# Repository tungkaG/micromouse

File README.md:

Code for Demo-mouse:

Current status:
Main control loop in timer interrupt (streamSensorData function):
1. update curr_cell or curr_heading, depending on the command that just took place (STOP, FORWARD, TURN_90_LEFT, TURN_90_RIGHT, TURN_180)
2. get next command (STOP, FORWARD, TURN_90_LEFT, TURN_90_RIGHT, TURN_180) using nextCmd(left_sensor_info, right_sensor_info, front_sensor_info)

Every time the mouse stops, the grid (details see below) is sent via UART and can be received using print_maze_and_send_forward_speed.py and 
the FORWARD_SPEED can be changed anytime by sending e.g. "<6>" via UART to the demomouse (i.e. sets FORWARD_SPEED to 6 rad/s)

The following only concerns highLevelPlanning.c :

In nextCmd(...): If the next cell is reached (curr_cell==next_cell), based on the state (IDLE, EXPLORING_PATH_TO_GOAL, EXPLORING_TEMP_BEST_PATH, RETURN_TO_START, DRIVE_TO_GOAL) the new next_cell is calculated:

EXPLORING_PATH_TO_GOAL: update grid matrix with sensor infos and find best next cell on the way to the goals (middle region) using Flood Fill Algorithm.

EXPLORING_TEMP_BEST_PATH: update grid matrix with sensor infos and find next cell with UNKNOWN walls that is part of the temporarily best path from start to goals.

RETURN_TO_START: update grid matrix with sensor infos and find best next cell on the way to cell {START_X, START_Y}

DRIVE_TO_GOAL: find best next cell on the path to goal using Flood Fill Algorithm

Then via translate_next_cell_to_cmd() check if the mouse should turn or if curr_heading == want_heading -> drive FORWARD

In general, grid is a matrix stored as grid[GRID_SIZE][GRID_SIZE][4], so for each cell, we store if UP, LEFT, DOWN and RIGHT (index 0 - 3) is WALL or is FREE. 

An example grid looks like this (note that y are the rows and x are the cols, so grid[curr_cell.y][curr_cell.x][UP] corresponds to the upper wall of the current cell:

' ' ' '
	UP

LEFT (x,y) RIGHT

' ' ' '
	DOWN

(0,0) (1,0)

(0,1)  ...

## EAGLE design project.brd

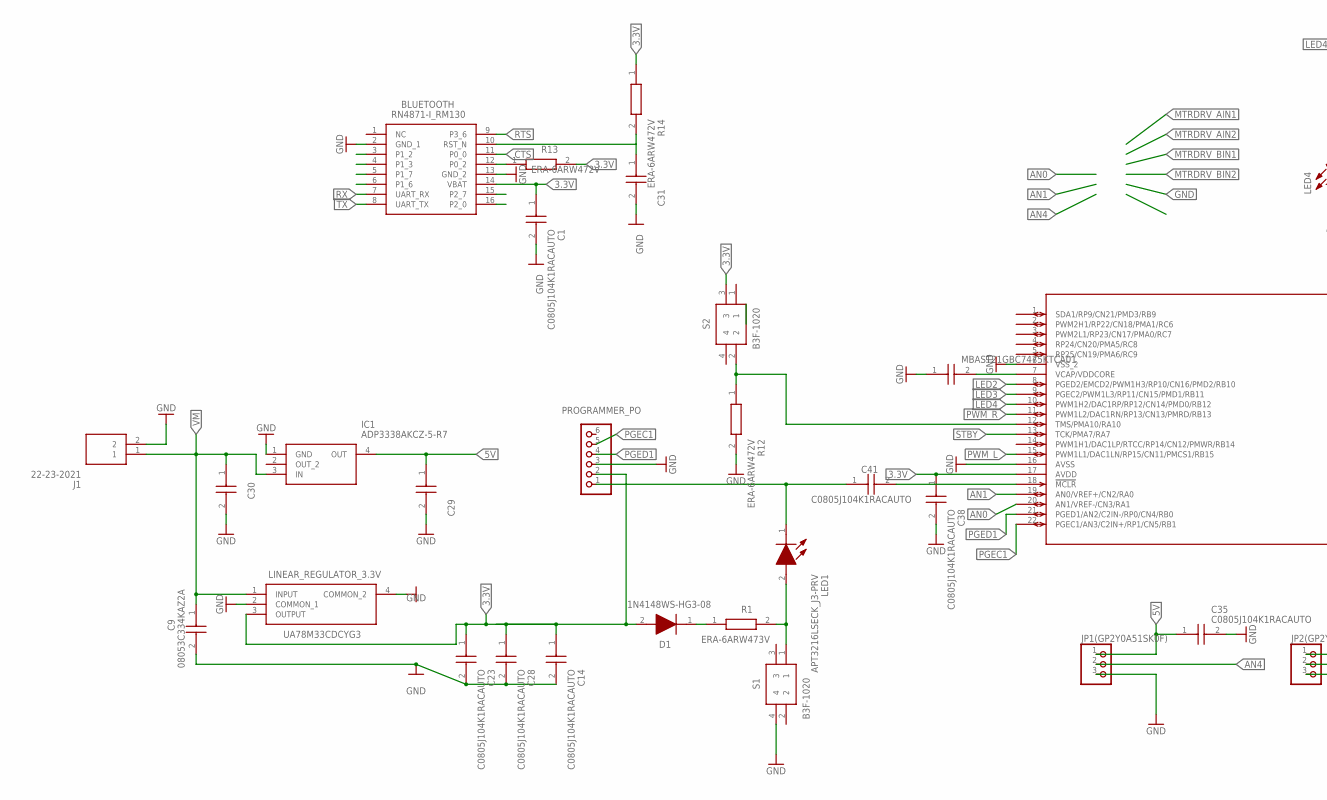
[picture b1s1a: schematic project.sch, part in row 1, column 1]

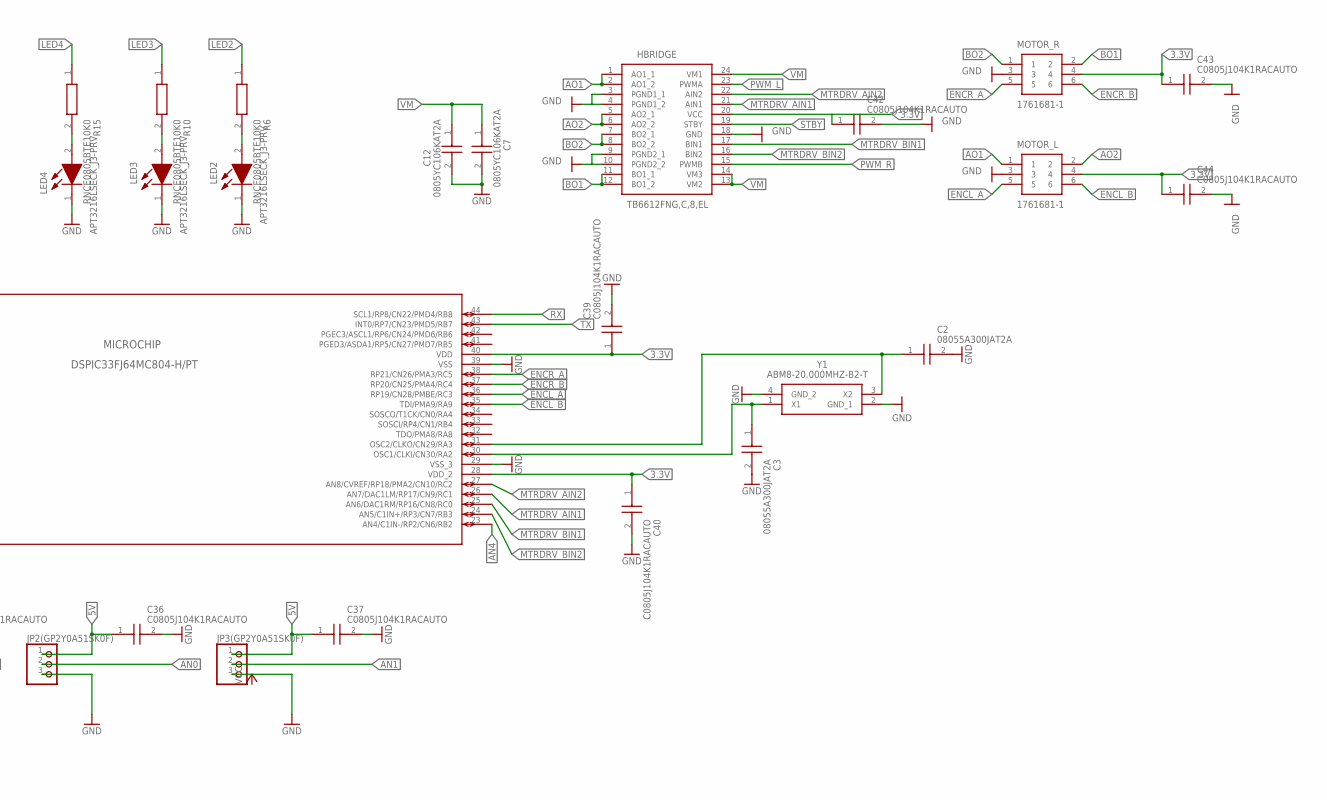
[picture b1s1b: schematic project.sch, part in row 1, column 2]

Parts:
BLUETOOTH: RN4871-I_RM130; RN4871
C1, C14, C23, C28, C29, C31, C35, C36, C37, C38, C39, C40, C41, C42, C43, C44: C0805J104K1RACAUTO; CAPC2012X140N
C2, C3: 08055A300JAT2A; CAPC2012X94N
C4: MBAST21GBC7475KTCA01; CAPC2114X145N
C7, C12: 0805YC106KAT2A; CAPC2012X94N
C9: 08053C334KAZ2A; CAPC2012X152N
C30: 1µF; CAPC2012X140N
D1: 1N4148WS-HG3-08; SOD2713X115N
HBRIDGE: TB6612FNG,C,8,EL; SOP65P760X160-24N
IC1: ADP3338AKCZ-5-R7; SOT230P700X180-4N
J1: 22-23-2021; SHDR2W87P0X254_1X2_493X635X110
JP1(GP2Y0A51SK0F), JP2(GP2Y0A51SK0F), JP3(GP2Y0A51SK0F): PINHD-1X3; 1X03
LED1, LED2, LED3, LED4: APT3216LSECK_J3-PRV; LEDC3216X95N
LINEAR_REGULATOR_3.3V: UA78M33CDCYG3; SOT230P700X180-4N
MICROCHIP: DSPIC33FJ64MC804-H/PT; TQFP44_10X10MC_MCH
MOTOR_L: 1761681-1; SHDR6W67P254_2X3_1524X916X922P
MOTOR_R: 1761681-1; SHDR6W67P254_2X3_1524X916X922P
PROGRAMMER_PO: PINHD-1X6; 1X06
R1: ERA-6ARW473V; ERA6AEB101V
R6, R10, R15: RNCE0805BTE10K0; RESC2012X65N
R12, R13, R14: ERA-6ARW472V; ERA6AEB101V
S1, S2: B3F-1020; B3F1000
Y1: ABM8-20.000MHZ-B2-T; ABM810000MHZ12D2W

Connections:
3.3V: BLUETOOTH.14 (VBAT), C1.1, C14.1, C23.1, C28.1, C38.1, C39.1, C40.1, C42.1, C43.1, C44.1, D1.2 (A), HBRIDGE.20 (VCC), LINEAR_REGULATOR_3.3V.3 (OUTPUT), MICROCHIP.17 (AVDD), MICROCHIP.28 (VDD_2), MICROCHIP.40 (VDD), MOTOR_L.4, MOTOR_R.4, PROGRAMMER_PO.2, R13.2, R14.1, S2.3
5V: C29.1, C35.1, C36.1, C37.1, IC1.4 (OUT), JP1(GP2Y0A51SK0F).1, JP2(GP2Y0A51SK0F).1, JP3(GP2Y0A51SK0F).1
AN0: JP2(GP2Y0A51SK0F).2, MICROCHIP.20 (AN1/VREF-/CN3/RA1)
AN1: JP3(GP2Y0A51SK0F).2, MICROCHIP.19 (AN0/VREF+/CN2/RA0)
AN4: JP1(GP2Y0A51SK0F).2, MICROCHIP.23 (AN4/C1IN-/RP2/CN6/RB2)
AO1: HBRIDGE.1 (AO1_1), HBRIDGE.2 (AO1_2), MOTOR_L.1
AO2: HBRIDGE.5 (AO2_1), HBRIDGE.6 (AO2_2), MOTOR_L.2
BO1: HBRIDGE.11 (BO1_1), HBRIDGE.12 (BO1_2), MOTOR_R.2
BO2: HBRIDGE.7 (BO2_1), HBRIDGE.8 (BO2_2), MOTOR_R.1
CTS: BLUETOOTH.11 (P0_0)
ENCL_A: MICROCHIP.36 (RP19/CN28/PMBE/RC3), MOTOR_L.5
ENCL_B: MICROCHIP.35 (TDI/PMA9/RA9), MOTOR_L.6
ENCR_A: MICROCHIP.38 (RP21/CN26/PMA3/RC5), MOTOR_R.5
ENCR_B: MICROCHIP.37 (RP20/CN25/PMA4/RC4), MOTOR_R.6
GND: BLUETOOTH.2 (GND_1), BLUETOOTH.13 (GND_2), C1.2, C2.2, C3.2, C4.1, C7.2, C9.2, C12.2, C14.2, C23.2, C28.2, C29.2, C30.2, C31.2, C35.2, C36.2, C37.2, C38.2, C39.2, C40.2, C42.2, C43.2, C44.2, HBRIDGE.3 (PGND1_1), HBRIDGE.4 (PGND1_2), HBRIDGE.9 (PGND2_1), HBRIDGE.10 (PGND2_2), HBRIDGE.18 (GND), IC1.1 (GND), J1.2, JP1(GP2Y0A51SK0F).3, JP2(GP2Y0A51SK0F).3, JP3(GP2Y0A51SK0F).3, LED2.1 (K), LED3.1 (K), LED4.1 (K), LINEAR_REGULATOR_3.3V.2 (COMMON_1), LINEAR_REGULATOR_3.3V.4 (COMMON_2), MICROCHIP.6 (VSS_2), MICROCHIP.16 (AVSS), MICROCHIP.29 (VSS_3), MICROCHIP.39 (VSS), MOTOR_L.3, MOTOR_R.3, PROGRAMMER_PO.3, R12.2, S1.4, Y1.2 (GND_1), Y1.4 (GND_2)
LED2: MICROCHIP.8 (PGED2/EMCD2/PWM1H3/RP10/CN16/PMD2/RB10), R6.1
LED3: MICROCHIP.9 (PGEC2/PWM1L3/RP11/CN15/PMD1/RB11), R10.1
LED4: MICROCHIP.10 (PWM1H2/DAC1RP/RP12/CN14/PMD0/RB12), R15.1
MTRDRV_AIN1: HBRIDGE.21 (AIN1), MICROCHIP.26 (AN7/DAC1LM/RP17/CN9/RC1)
MTRDRV_AIN2: HBRIDGE.22 (AIN2), MICROCHIP.27 (AN8/CVREF/RP18/PMA2/CN10/RC2)
MTRDRV_BIN1: HBRIDGE.17 (BIN1), MICROCHIP.25 (AN6/DAC1RM/RP16/CN8/RC0)
MTRDRV_BIN2: HBRIDGE.16 (BIN2), MICROCHIP.24 (AN5/C1IN+/RP3/CN7/RB3)
unnamed: C2.1, MICROCHIP.31 (OSC2/CLKO/CN29/RA3), Y1.3 (X2)
unnamed: C3.1, MICROCHIP.30 (OSC1/CLKI/CN30/RA2), Y1.1 (X1)
unnamed: D1.1 (K), R1.1
unnamed: LED4.2 (A), R15.2
unnamed: C4.2, MICROCHIP.7 (VCAP/VDDCORE)
unnamed: C41.1, LED1.1 (K), PROGRAMMER_PO.1
unnamed: LED3.2 (A), R10.2
unnamed: LED2.2 (A), R6.2
unnamed: LED1.2 (A), R1.2, S1.1
unnamed: C41.2, MICROCHIP.18 (!MCLR)
unnamed: MICROCHIP.12 (TMS/PMA10/RA10), R12.1, S2.2
unnamed: BLUETOOTH.10 (RST_N), C31.1, R14.2
unnamed: BLUETOOTH.12 (P0_2), R13.1
PGEC1: MICROCHIP.22 (PGEC1/AN3/C2IN+/RP1/CN5/RB1), PROGRAMMER_PO.5
PGED1: MICROCHIP.21 (PGED1/AN2/C2IN-/RP0/CN4/RB0), PROGRAMMER_PO.4
PWM_L: HBRIDGE.23 (PWMA), MICROCHIP.15 (PWM1L1/DAC1LN/RP15/CN11/PMCS1/RB15)
PWM_R: HBRIDGE.15 (PWMB), MICROCHIP.11 (PWM1L2/DAC1RN/RP13/CN13/PMRD/RB13)
RTS: BLUETOOTH.9 (P3_6)
RX: BLUETOOTH.7 (UART_RX), MICROCHIP.44 (SCL1/RP8/CN22/PMD4/RB8)
STBY: HBRIDGE.19 (STBY), MICROCHIP.13 (TCK/PMA7/RA7)
TX: BLUETOOTH.8 (UART_TX), MICROCHIP.43 (INT0/RP7/CN23/PMD5/RB7)
VM: C7.1, C9.1, C12.1, C30.1, HBRIDGE.13 (VM2), HBRIDGE.14 (VM3), HBRIDGE.24 (VM1), IC1.3 (IN), J1.1, LINEAR_REGULATOR_3.3V.1 (INPUT)

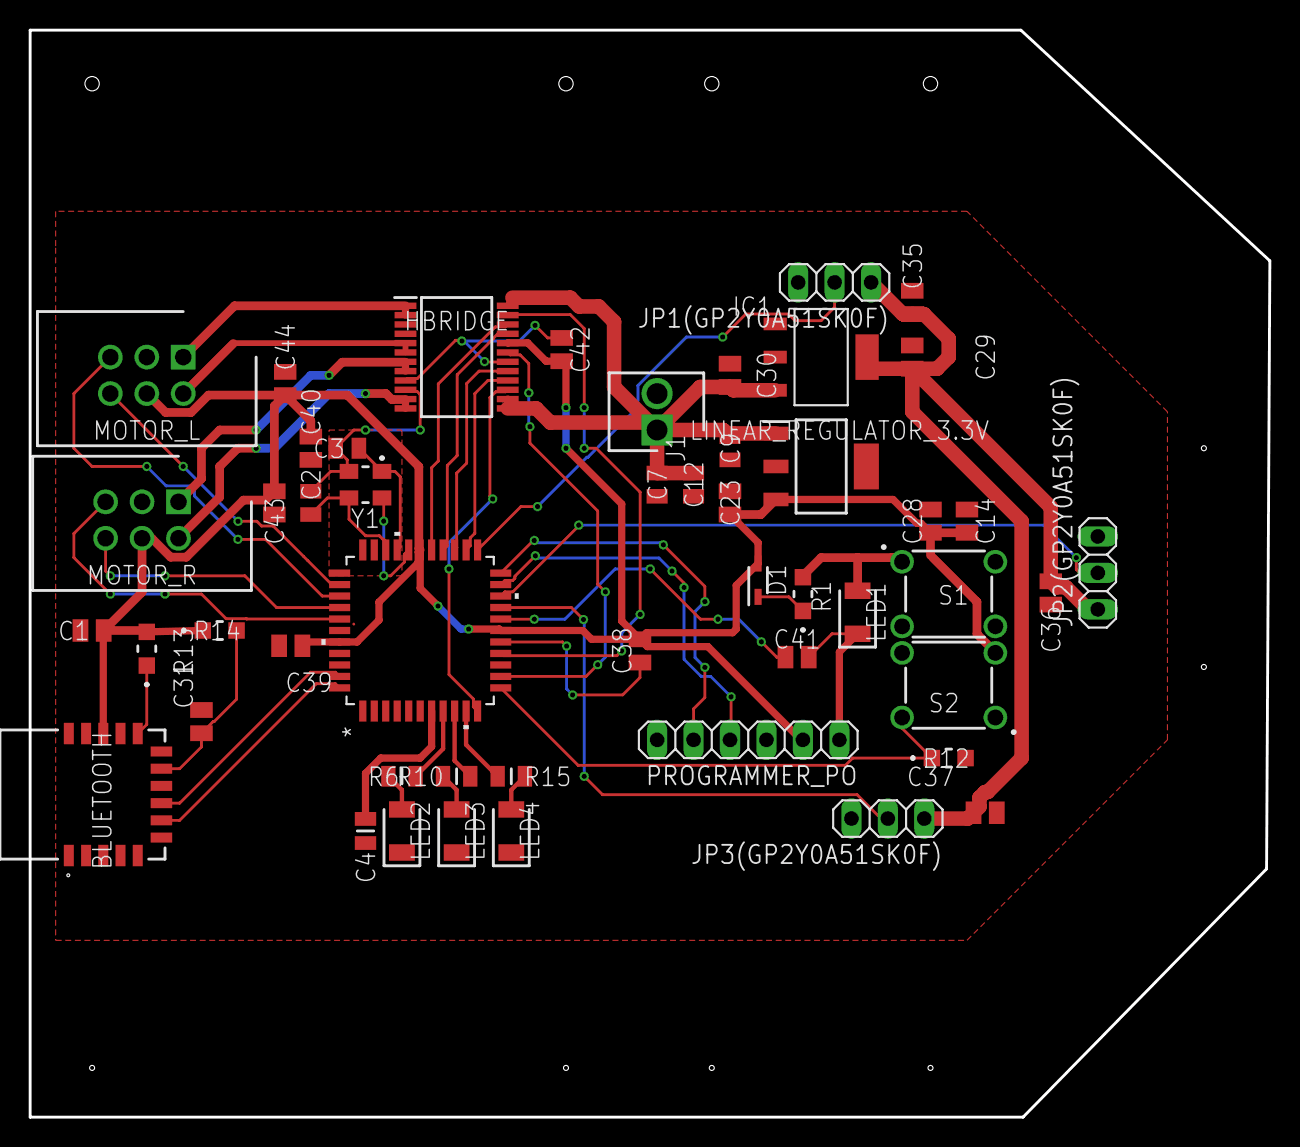
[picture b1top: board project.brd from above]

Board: 2 copper layers, 86.4 x 75.7 mm, 50 parts (0 on the bottom side), 42 nets.

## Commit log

2025-06-24 initial source commit with UART and Motor Encoder
2025-07-08 init
2025-07-10 add external oscillator
2025-07-10 connect the other 2 sensors
2025-07-10 add motor driver
2025-07-10 add UAB_UART converter
2025-07-13 Design Rules2
2025-07-15 Motor Pinout
2025-07-15 Motor Pinout in Schematic
2025-07-15 add motor, leds, debug pins, replace USBUART with bluetooth ver.
2025-07-16 first version of maze solving algorithm (find_nearest_unknown A*star) + control
2025-07-16 corrected led/lin regulator elements
2025-07-17 flood field algorithm + smooth braking after last_forward implemented
2025-07-18 Removed Liner Regulator
2025-07-19 Linear Regulator Added
2025-07-19 Renamed Components
2025-07-19 kleine Änderungen
2025-07-20 HBridge Verändert
2025-07-21 Oscillator
2025-07-22 Schematic Vollständig?
2025-07-22 Board Created
2025-07-22 All components placed
2025-07-22 rename ENCA and ENCB, remap PWM pins
2025-07-22 add 5V voltage regulator
2025-07-22 find_unknown_in_provisional_path added + calc_provisional_path reworked
2025-07-25 Leds added, 5v Regulator Moved, Bluetooth removed
2025-07-26 Small Changes
2025-07-26 Added Bluetooth Module
2025-07-27 group and place components in board
2025-07-27 route board
2025-07-29 added return statement after finishing maze
2025-07-29 changed path[] to next_cell
2025-07-29 refactored code + Grid sent via UART_TX + FORWARD_SPEED set via UART_RX
2025-07-29 added script to print curr grid to terminal
2025-07-29 Update README.md corresponding to refactoring
2025-08-03 Progress!
2025-08-03 Progress
2025-08-04 Saving Progress
2025-08-04 review #1
2025-08-05 Fertig?
2025-08-05 Vorderes Bohrloch Geändert

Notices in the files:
parts and their libraries:
COPYRIGHT: Copyright (C) 2025 Ultra Librarian. All rights reserved.
